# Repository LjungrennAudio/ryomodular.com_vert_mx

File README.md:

# ryomodular.com_vert_mx
 yet another new ryomodule - thi time the lon overdue vertmix mixer

2408302315

this is the repo for the ryodular.com vert_mx urorack format modular synth mixer module.

its been around as a prototypefor near 13 years and even visible on mod grid etc. yet never released so i guess it's about time really...

it's not much exciting am afraid - a 3 channel mixer with attenu version on each channel as well asbreakout signal option to allow just utility use without being used as a mixer.

it will  be available in ht new white panel/gold markings n pink knobs plus green leds along with the traditional ryo colourscheme too.
it should  be a pretty low price basic beginner DIY build friendly kinda module as oer ryo's traditional so far iutput so may not catch as much attention as the other new modules in the lineup but i feel c9mpelled to bring this cha[pter to closure at whatever cost the way things seem to be going. : D

if anyone cn come up with real exciting patch progaramming uses or unusuial thoughts for patch examples please tell me cos am not super inspired by thios one tbh - it's absolutely an essential you cnt do without in a system but it's not exactly the kimda thing you shout about - it just sits queitly in the corner doing it's job and eing an unsung hero of the modular ecosystem.

this will be cheap, unexciting and solid. it needs to e there as oart of the lineup but its not a weird quirky one or some kind of flagship - it just is.

202501080338 addendum

this is p much exactly the same story as the repos for the other modules of the set 'vert_mx, dp_switch, adda. brit_eq5', - i.e. it's not finished until it's finished and i aint attempting to bring order to chaos until it's all over so for now this aint gonna be sereing alotta change except for even more files being added. sorro.

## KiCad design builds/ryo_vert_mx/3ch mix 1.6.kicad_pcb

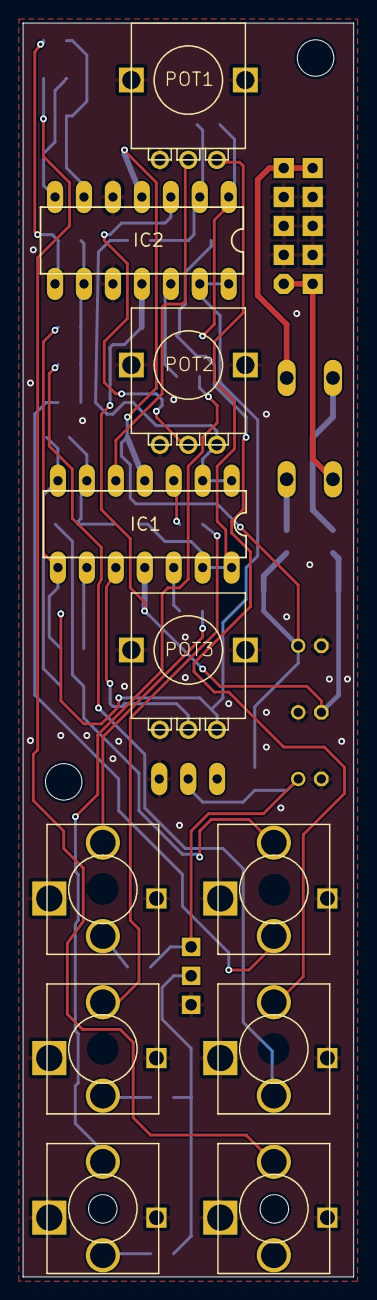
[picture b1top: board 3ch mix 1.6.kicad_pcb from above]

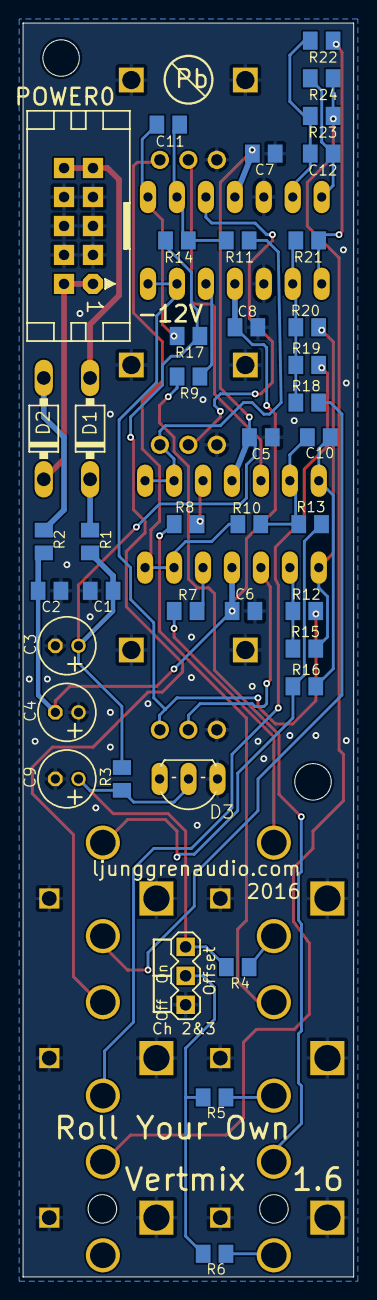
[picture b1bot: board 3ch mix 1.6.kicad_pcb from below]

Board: 2 copper layers, 29.0 x 110.0 mm, 56 parts (41 on the bottom side), 39 nets.

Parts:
@HOLE0, @HOLE1, @HOLE2, @HOLE3: (no value)
C1, C2, C5, C6, C7, C8: 100nF; C0805K
C3, C4, C9: 10uF; E2-5
C10, C11, C12: 68pF; C0805K
D1, D2: 1N5818; DO41-7
D3: LM4040 5V; TO92-LINE
IC1, IC2: TL084; DIL14
IN1, IN2, IN3: ERTHENVAR_3.5MM_JACKHOLES; ERTHENVAR
JP1: MA03-1
OUT1, OUT2, OUT3: ERTHENVAR_3.5MM_JACKHOLES; ERTHENVAR
POT1, POT2, POT3: 22K; POT-ALPHA9
POWER0: CON10L
R1, R2: 10R; C0805K
R3: 10K; C0805K
R4, R5, R6, R7, R8, R9, R10, R11, R12, R13, R14, R15, R18, R19, R20, R21, R22, R23: 22K; C0805K
R16, R17, R24: 330R; C0805K

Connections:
0V: C1.2, C2.1, C3.-, C4.+, C5.2, C6.1, C7.2, C8.1, C9.-, D3.3, IC2.5, IC2.10, IN1.RING1, IN1.RING2, IN2.RING1, IN2.RING2, IN3.RING1, IN3.RING2, JP1.1, OUT1.RING1, OUT1.RING2, OUT2.RING1, OUT2.RING2, OUT3.RING1, OUT3.RING2, POT1.GND$1, POT1.GND$2, POT1.LEFT, POT2.GND$1, POT2.GND$2, POT2.LEFT, POT3.GND$1, POT3.GND$2, POT3.LEFT, POWER0.3, POWER0.4, POWER0.5, POWER0.6, POWER0.7, POWER0.8
+12V: C1.1, C3.+, C5.1, C7.1, IC1.4, IC2.4, R1.2, R3.2
-12V: C2.2, C4.-, C6.2, C8.2, IC1.11, IC2.11, R2.2
unnamed: D1.A, POWER0.9, POWER0.10
unnamed: D2.C, POWER0.1, POWER0.2
unnamed: IC2.8, R21.2, R22.1
unnamed: C12.1, IC2.6, R22.2, R23.1
unnamed: D1.C, R1.1
unnamed: D2.A, R2.1
unnamed: C9.+, D3.2, JP1.3, R3.1, R4.1
unnamed: OUT1.TIP, R13.2, R16.2
unnamed: IC1.12, R7.2
unnamed: IC1.3, R8.2
unnamed: IC2.12, R9.2
unnamed: IC1.13, IC1.14, POT1.RIGHT, R10.1
unnamed: IC1.1, IC1.2, POT2.RIGHT, R11.1
unnamed: IC2.13, IC2.14, POT3.RIGHT, R12.1
unnamed: C10.2, IC1.6, R10.2, R13.1
unnamed: IC1.5, POT1.MID
unnamed: IC2.3, POT2.MID
unnamed: IC1.10, POT3.MID
unnamed: OUT2.TIP, R14.2, R17.2
unnamed: IN1.TIP, R7.1
unnamed: C11.2, IC2.2, R11.2, R14.1
unnamed: IC1.9, R12.2, R15.1
unnamed: OUT3.TIP, R23.2, R24.2
unnamed: IN2.TIP, R8.1
unnamed: IC1.8, R15.2, R20.1
unnamed: OUT1.SHUNT, R18.1
unnamed: OUT2.SHUNT, R19.1
unnamed: IC2.9, R18.2, R19.2, R20.2, R21.1
unnamed: C12.2, IC2.7, R24.1
unnamed: IN1.SHUNT, R4.2
unnamed: IN2.SHUNT, R5.2
unnamed: IN3.SHUNT, R6.2
unnamed: JP1.2, R5.1, R6.1
unnamed: IN3.TIP, R9.1
unnamed: C10.1, IC1.7, R16.1
unnamed: C11.1, IC2.1, R17.1

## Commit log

2024-08-30 init commit or ryomldular.com vert_mx
    as usual the init commit is a mess of random unsorted carnage that eventually gets cleaned and tidied and generally sorted into a pro[er project poeple can make sense of...
2024-09-06 added a coupla files i guess
2024-09-29 create vert_mx gerbers.zip
    shop asked for repeats /shrug
2024-10-02 tidying up mess from init commit
    just filing things away into neat lil folders
2024-11-05 only promo after this
    can tidy up soon
2024-12-23 blue dot
    blu
2025-01-07 new crap added npow it's released and fuinally off my radar
    good to see end of this - now i can tidy this gitinto a comprhensible state
2025-01-08 t i d y
    omg for realz
2025-01-12 added docs
2025-01-13 wow a lotta stuff
    dunno what
2025-01-13 filing
